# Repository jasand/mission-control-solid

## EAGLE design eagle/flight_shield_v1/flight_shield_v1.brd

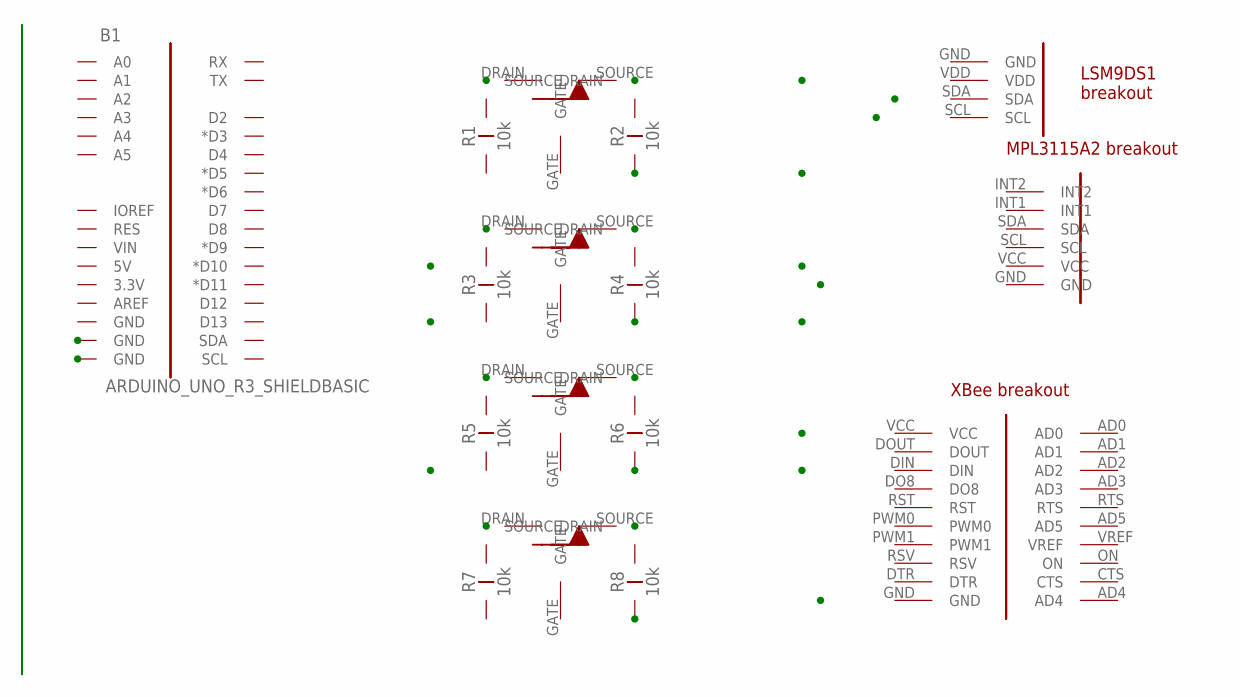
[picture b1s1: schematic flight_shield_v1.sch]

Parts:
B1: ARDUINO_UNO_R3_SHIELDBASIC; UNO_R3_SHIELD
R1, R2, R3, R4, R5, R6, R7, R8: 10k; AXIAL-0.3
U$1: LSM9DS1-BREAKOUT
U$2: MPL3115A2-BREAKOUT
U$3: XBEE-MODULE; XBEE-DIL20
U$4, U$5, U$6, U$7: 5LN01SP_NMOS

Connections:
unnamed: B1.GND@0 (GND), B1.GND@1 (GND), B1.GND@2 (GND), U$1.GND, U$2.GND, U$3.GND
unnamed: B1.3.3V, R2.P$1 (1), R4.P$1 (1), R6.P$1 (1), R8.P$1 (1), U$1.VDD, U$2.VCC, U$3.VCC, U$4.GATE, U$5.GATE, U$6.GATE, U$7.GATE
unnamed: B1.SDA, R1.P$2 (2), U$4.DRAIN
unnamed: R2.P$2 (2), U$1.SDA, U$2.SDA, U$4.SOURCE
unnamed: R4.P$2 (2), U$1.SCL, U$2.SCL, U$5.SOURCE
unnamed: B1.SCL, R3.P$2 (2), U$5.DRAIN
unnamed: R6.P$2 (2), U$3.DOUT, U$6.SOURCE
unnamed: B1.D2, R5.P$2 (2), U$6.DRAIN
unnamed: R8.P$2 (2), U$3.DIN, U$7.SOURCE
unnamed: B1.D3 (*D3), R7.P$2 (2), U$7.DRAIN
unnamed: B1.5V, R1.P$1 (1), R3.P$1 (1), R5.P$1 (1), R7.P$1 (1)

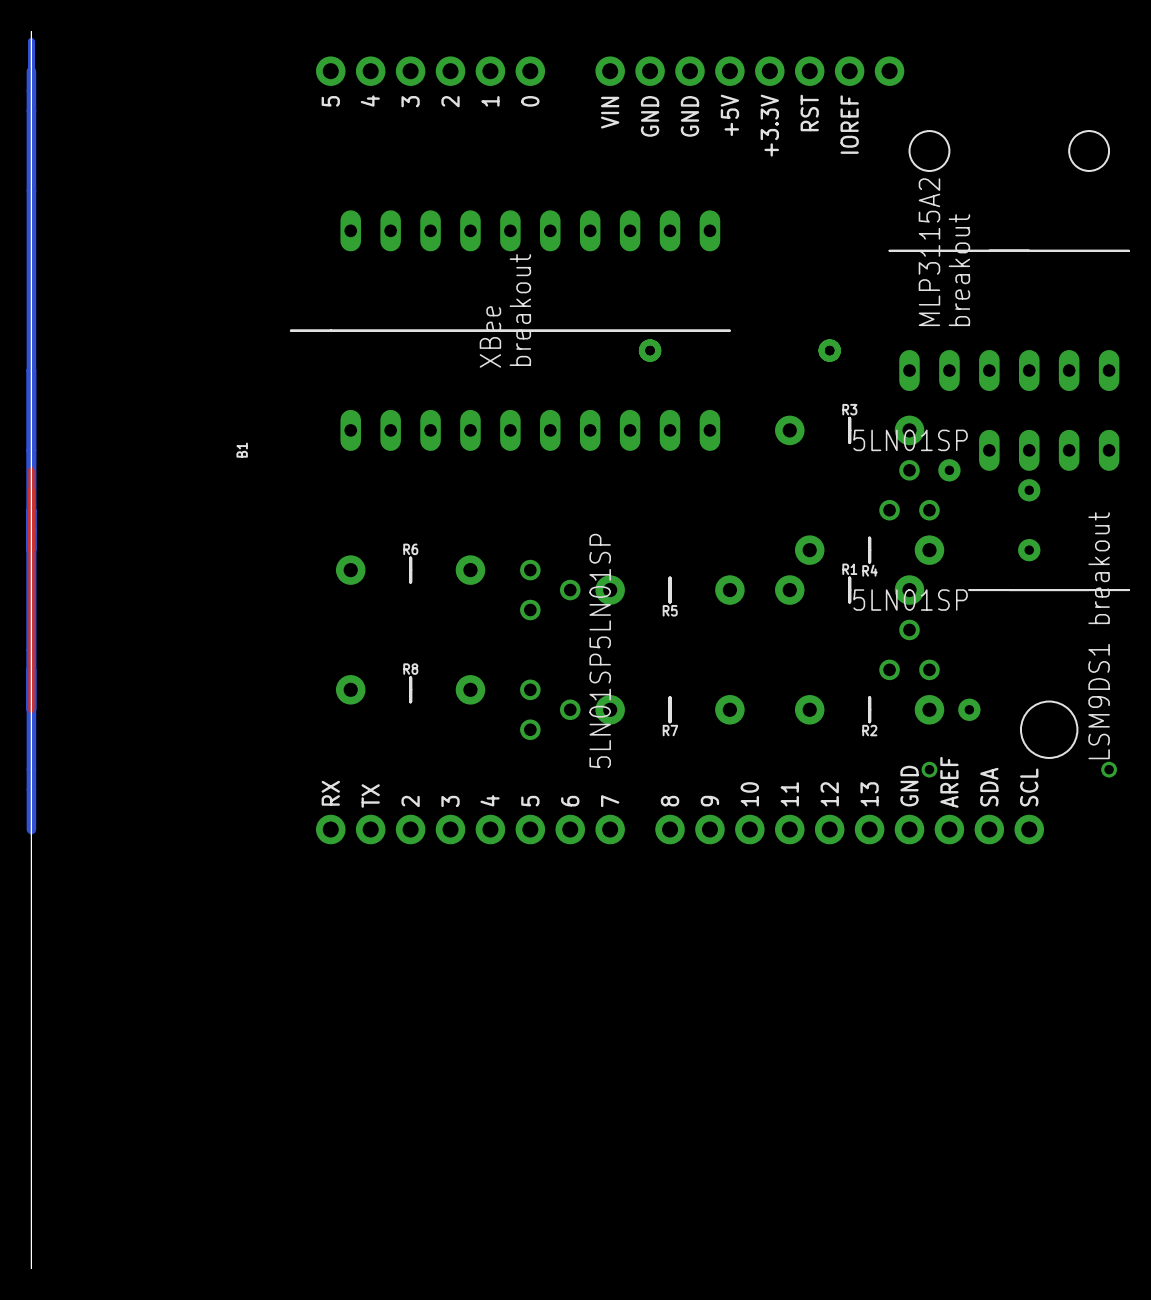
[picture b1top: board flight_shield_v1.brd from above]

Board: 2 copper layers, 16 parts (0 on the bottom side), 11 nets.

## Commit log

2017-02-10 Fxml
2017-02-15 Mer eller mindre migrert til fxml
2017-02-16 Lagt til initialisering og baseline verdier.
2017-02-16 Added arduino and eagle files
2017-02-19 updated gitignore
2017-02-19 Started on history tab
2017-02-28 Basic fillesing og min / max akselerasjon
2018-08-18 Commit endringer før videre arbeid
2018-08-21 Ymse endringer. Testet med flight board, XBee Pro og 57600 baud. Litt nærmere nå...
2018-08-27 IMU / AHRS prosessering begynner å bli bedre. Flyttet arduino filer til git.
2018-08-27 Endre sampling til 20Hz
2018-08-30 Rotasjonsmatrise og MeshView
2018-08-31 TextureMap
2018-11-11 AHRS looking a little bit better. Needs more tuning.
2019-02-26 Added program for rocket AHRS testing.
2019-02-26 Added texture map for rocket.
2019-03-01 Rocket for visualization done.
2019-03-02 Added rocket to main view.
2019-03-03 Modified states and started integration of application and controller code.

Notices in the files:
parts and their libraries:
SparkFun-Boards: Licensing: Creative Commons ShareAlike 4.0 International - https://creativecommons.org/licenses/by-sa/4.0
